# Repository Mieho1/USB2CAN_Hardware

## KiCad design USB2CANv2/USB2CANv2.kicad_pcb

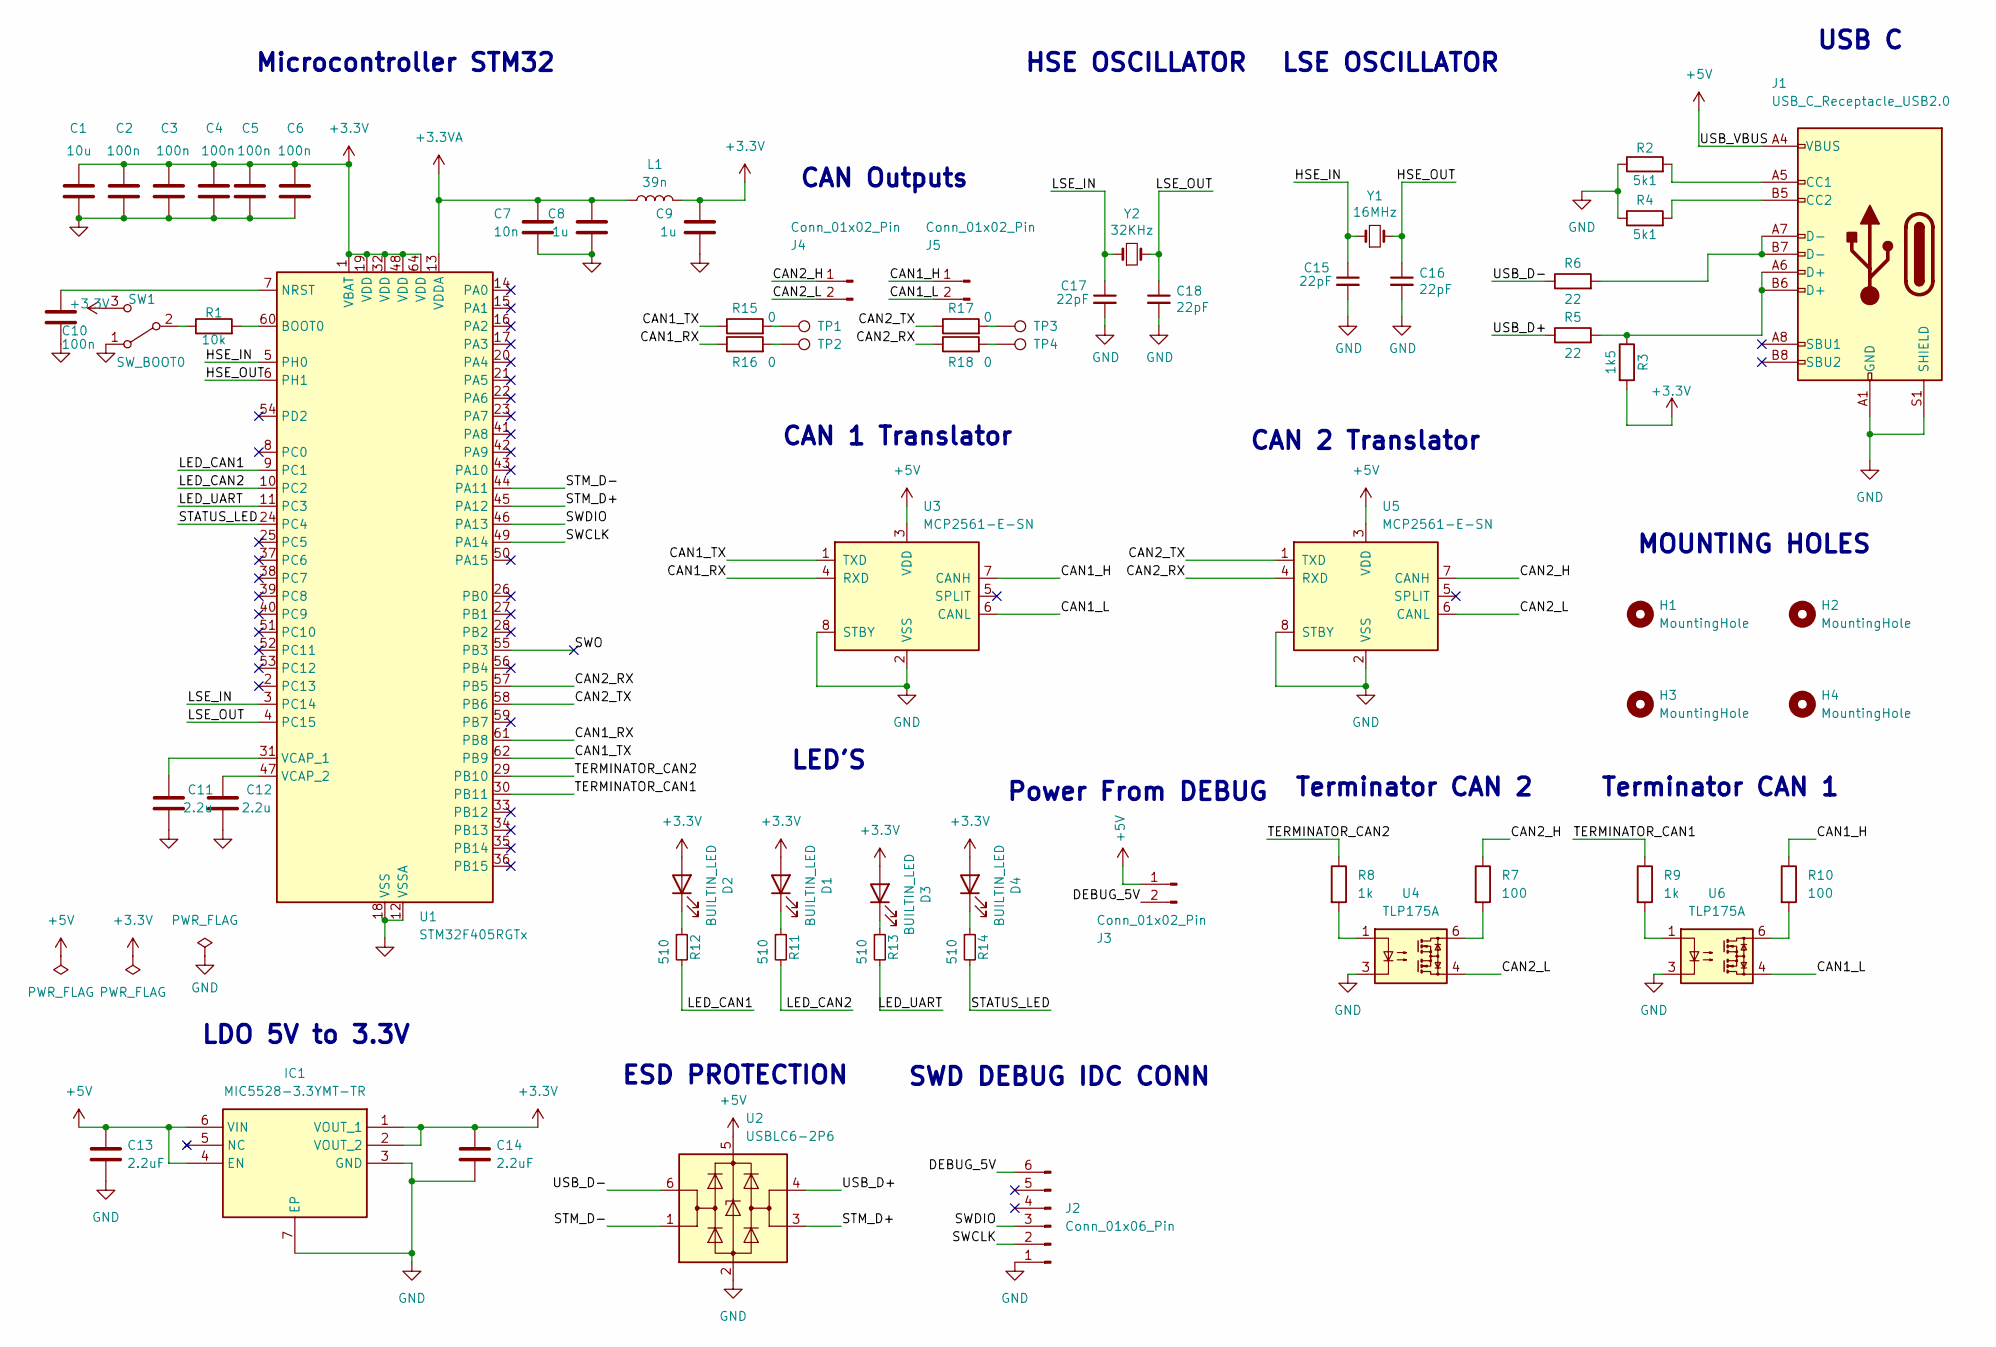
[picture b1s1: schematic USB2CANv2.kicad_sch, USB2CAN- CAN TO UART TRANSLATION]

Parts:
C1: 10u; C_0402_1005Metric_Pad0.74x0.62mm_HandSolder
C2, C3, C4, C5, C6, C10: 100n; C_0402_1005Metric_Pad0.74x0.62mm_HandSolder
C7: 10n; C_0402_1005Metric_Pad0.74x0.62mm_HandSolder
C8, C9: 1u; C_0402_1005Metric_Pad0.74x0.62mm_HandSolder
C11, C12: 2.2u; C_0402_1005Metric_Pad0.74x0.62mm_HandSolder
C13, C14: 2.2uF; C_0402_1005Metric
C15, C16, C17, C18: 22pF; C_0402_1005Metric_Pad0.74x0.62mm_HandSolder
D1, D2, D3, D4: BUILTIN_LED; LED_0805_2012Metric
H1, H2, H3, H4: MountingHole; MountingHole_2.1mm
IC1: MIC5528-3.3YMT-TR; SON40P120X120X60-7N-D; Mouser Part Number 998-MIC5528-3.3YMTTR
J1: USB_C_Receptacle_USB2.0; USB_C_Receptacle_GCT_USB4085
J2: Conn_01x06_Pin; IDC_SMD_3PIN
J3, J4, J5: Conn_01x02_Pin; PinHeader_1x02_P2.54mm_Vertical
L1: 39n; L_0805_2012Metric_Pad1.15x1.40mm_HandSolder
R1: 10k; R_0402_1005Metric_Pad0.72x0.64mm_HandSolder
R2, R4: 5k1; R_0603_1608Metric
R3: 1k5; R_0603_1608Metric
R5, R6: 22; R_0603_1608Metric
R7, R10: 100; R_0603_1608Metric
R8, R9: 1k; R_0603_1608Metric
R11, R12, R13, R14: 510; R_0402_1005Metric_Pad0.72x0.64mm_HandSolder
R15, R16, R17, R18: 0; R_0402_1005Metric_Pad0.72x0.64mm_HandSolder
SW1: SW_BOOT0; SolderJumper-3_P1.3mm_Open_RoundedPad1.0x1.5mm_NumberLabels
TP1, TP2, TP3, TP4: TestPoint; TestPoint_Pad_1.5x1.5mm
U1: STM32F405RGTx; LQFP-64_10x10mm_P0.5mm
U2: USBLC6-2P6; SOT-666
U3, U5: MCP2561-E-SN; SOIC-8_3.9x4.9mm_P1.27mm
U4, U6: TLP175A; MFSOP6-4_4.4x3.6mm_P1.27mm
Y1: 16MHz; Crystal_SMD_5032-2Pin_5.0x3.2mm
Y2: 32KHz; Crystal_SMD_3215-2Pin_3.2x1.5mm

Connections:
+3.3V: C1.1, C2.1, C3.1, C4.1, C5.1, C6.1, C9.1, C14.1, D1.2 (A), D2.2 (A), D3.2 (A), D4.2 (A), IC1.1 (VOUT_1), IC1.2 (VOUT_2), L1.2, R3.2, SW1.3 (C), U1.1 (VBAT), U1.19 (VDD), U1.32 (VDD), U1.48 (VDD), U1.64 (VDD)
+3.3VA: C7.1, C8.1, L1.1, U1.13 (VDDA)
+5V: C13.1, IC1.4 (EN), IC1.6 (VIN), J1.A4 (VBUS), J1.A9 (VBUS), J1.B4 (VBUS), J1.B9 (VBUS), J3.1, U2.5 (VBUS), U3.3 (VDD), U5.3 (VDD)
/CAN1_H: J5.1, R10.1, U3.7 (CANH)
/CAN1_L: J5.2, U3.6 (CANL), U6.4
/CAN1_RX: R16.1, U1.61 (PB8), U3.4 (RXD)
/CAN1_TX: R15.1, U1.62 (PB9), U3.1 (TXD)
/CAN2_H: J4.1, R7.1, U5.7 (CANH)
/CAN2_L: J4.2, U4.4, U5.6 (CANL)
/CAN2_RX: R18.1, U1.57 (PB5), U5.4 (RXD)
/CAN2_TX: R17.1, U1.58 (PB6), U5.1 (TXD)
/DEBUG_5V: J2.6, J3.2
/HSE_IN: C15.1, U1.5 (PH0), Y1.1
/HSE_OUT: C16.1, U1.6 (PH1), Y1.2
/LED_CAN1: R12.2, U1.9 (PC1)
/LED_CAN2: R11.2, U1.10 (PC2)
/LED_UART: R13.2, U1.11 (PC3)
/LSE_IN: C17.1, U1.3 (PC14), Y2.1
/LSE_OUT: C18.1, U1.4 (PC15), Y2.2
/STATUS_LED: R14.2, U1.24 (PC4)
/STM_D+: U1.45 (PA12), U2.3 (I/O2)
/STM_D-: U1.44 (PA11), U2.1 (I/O1)
/SWCLK: J2.2, U1.49 (PA14)
/SWDIO: J2.3, U1.46 (PA13)
/SWO: U1.55 (PB3)
/TERMINATOR_CAN1: R9.1, U1.30 (PB11)
/TERMINATOR_CAN2: R8.1, U1.29 (PB10)
/USB_D+: R5.1, U2.4 (I/O2)
/USB_D-: R6.1, U2.6 (I/O1)
GND: C1.2, C2.2, C3.2, C4.2, C5.2, C6.2, C7.2, C8.2, C9.2, C10.2, C11.2, C12.2, C13.2, C14.2, C15.2, C16.2, C17.2, C18.2, IC1.3 (GND), IC1.7 (EP), J1.A1 (GND), J1.A12 (GND), J1.B1 (GND), J1.B12 (GND), J1.S1 (SHIELD), J2.1, R2.1, R4.1, SW1.1 (A), U1.12 (VSSA), U1.18 (VSS), U1.63 (VSS), U2.2 (GND), U3.2 (VSS), U3.8 (STBY), U4.3, U5.2 (VSS), U5.8 (STBY), U6.3
unnamed: D1.1 (K), R11.1
unnamed: D2.1 (K), R12.1
unnamed: D3.1 (K), R13.1
unnamed: D4.1 (K), R14.1
unnamed: J1.A5 (CC1), R2.2
unnamed: J1.B5 (CC2), R4.2
unnamed: J1.A6 (D+), J1.B6 (D+), R3.1, R5.2
unnamed: J1.A7 (D-), J1.B7 (D-), R6.2
unnamed: R7.2, U4.6
unnamed: R8.2, U4.1
unnamed: R9.2, U6.1
unnamed: R10.2, U6.6
unnamed: R15.2, TP1.1
unnamed: R16.2, TP2.1
unnamed: R17.2, TP3.1
unnamed: R18.2, TP4.1
unnamed: R1.1, SW1.2 (B)
unnamed: R1.2, U1.60 (BOOT0)
unnamed: C10.1, U1.7 (NRST)
unnamed: C11.1, U1.31 (VCAP_1)
unnamed: C12.1, U1.47 (VCAP_2)

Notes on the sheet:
Microcontroller STM32
Power From DEBUG
CAN 2 Translator
LED'S
MOUNTING HOLES
CAN Outputs
SWD DEBUG IDC CONN
USB C
Terminator CAN 2
LSE OSCILLATOR
LDO 5V to 3.3V
Terminator CAN 1
CAN 1 Translator
ESD PROTECTION
HSE OSCILLATOR

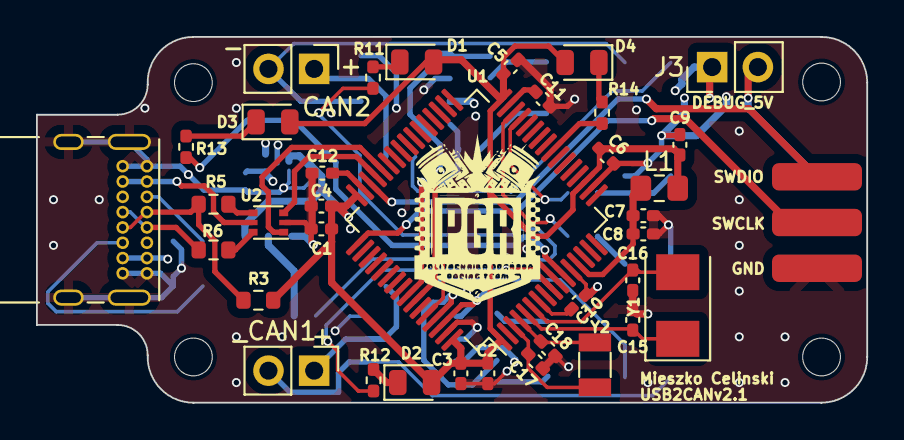
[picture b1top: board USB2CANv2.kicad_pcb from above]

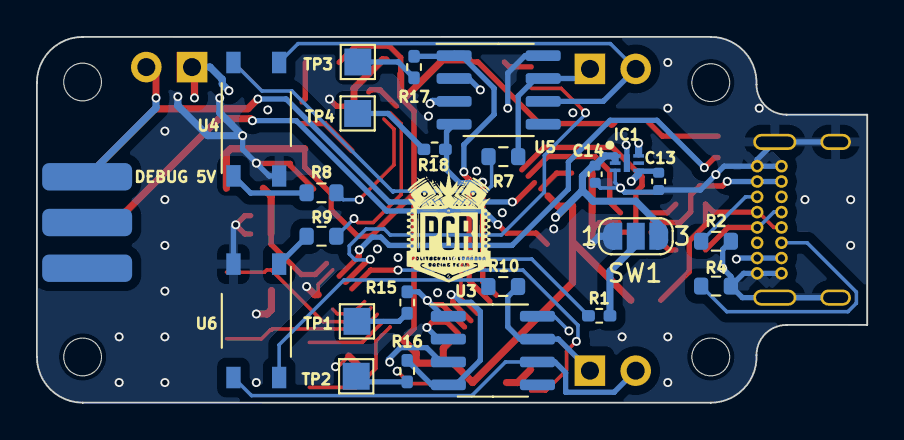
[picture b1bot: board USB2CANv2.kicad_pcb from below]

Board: 4 copper layers, 46.1 x 20.3 mm, 64 parts (23 on the bottom side), 50 nets.

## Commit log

2024-01-03 Added microcontroler
2024-01-07 Added most of needed components, from previous scheme.
2024-01-10 Done scheme
2024-01-10 Footprints added
2024-01-18 Creating PCB
2024-02-06 Placement done
    Placement done, started routing
2024-02-06 board routed
2024-02-06 All DRC warnings and errors deleted
2024-02-06 Board done
2024-02-06 Generated gerber files
2025-04-14 Changed stack-up, Silkscreen improvments + LSE HSE SWAP
2025-04-14 schematic revision updated
2025-04-14 Gerbers generated
